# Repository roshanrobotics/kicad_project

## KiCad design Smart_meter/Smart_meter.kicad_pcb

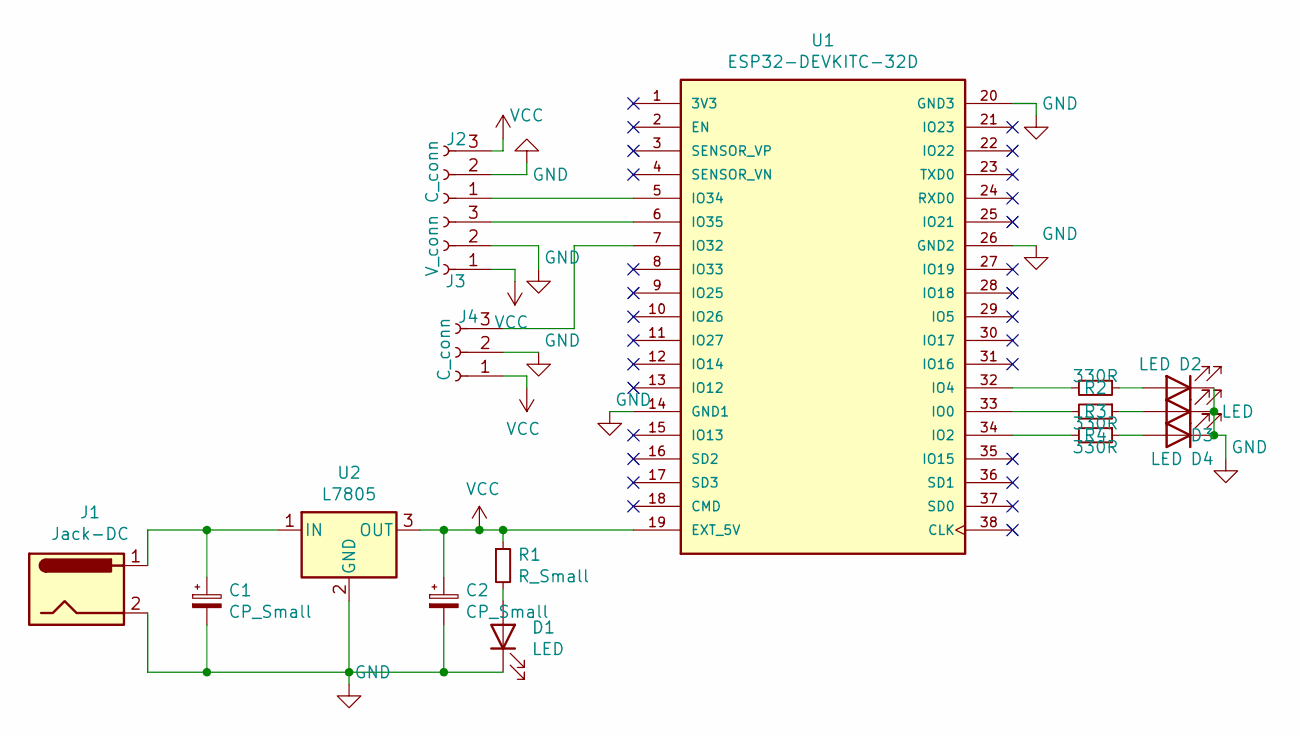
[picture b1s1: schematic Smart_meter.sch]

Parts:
C1, C2: CP_Small; CP_Radial_D5.0mm_P2.50mm
D1, D2, D3, D4: LED; LED_D5.0mm
J1: Jack-DC; BarrelJack_Horizontal
J2, J4: C_conn; PinHeader_1x03_P2.54mm_Vertical
J3: V_conn; PinHeader_1x03_P2.54mm_Vertical
R1: R_Small; R_Axial_DIN0207_L6.3mm_D2.5mm_P7.62mm_Horizontal
R2, R3, R4: 330R; R_Axial_DIN0207_L6.3mm_D2.5mm_P7.62mm_Horizontal
U1: ESP32-DEVKITC-32D; MODULE_ESP32-DEVKITC-32D; PARTREV 4
U2: L7805; TO-220-3_Vertical

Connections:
GND: C1.2, C2.2, D1.1 (K), D2.1 (K), D3.1 (K), D4.1 (K), J1.2, J2.2, J3.2, J4.2, U1.14 (GND1), U1.20 (GND3), U1.26 (GND2), U2.2 (GND)
unnamed: C1.1, J1.1, U2.1 (IN)
unnamed: D1.2 (A), R1.2
unnamed: D2.2 (A), R2.1
unnamed: D3.2 (A), R3.1
unnamed: D4.2 (A), R4.1
unnamed: J2.1, U1.5 (IO34)
unnamed: J3.3, U1.6 (IO35)
unnamed: J4.3, U1.7 (IO32)
unnamed: R2.2, U1.32 (IO4)
unnamed: R3.2, U1.33 (IO0)
unnamed: R4.2, U1.34 (IO2)
VCC: C2.1, J2.3, J3.1, J4.1, R1.1, U1.19 (EXT_5V), U2.3 (OUT)

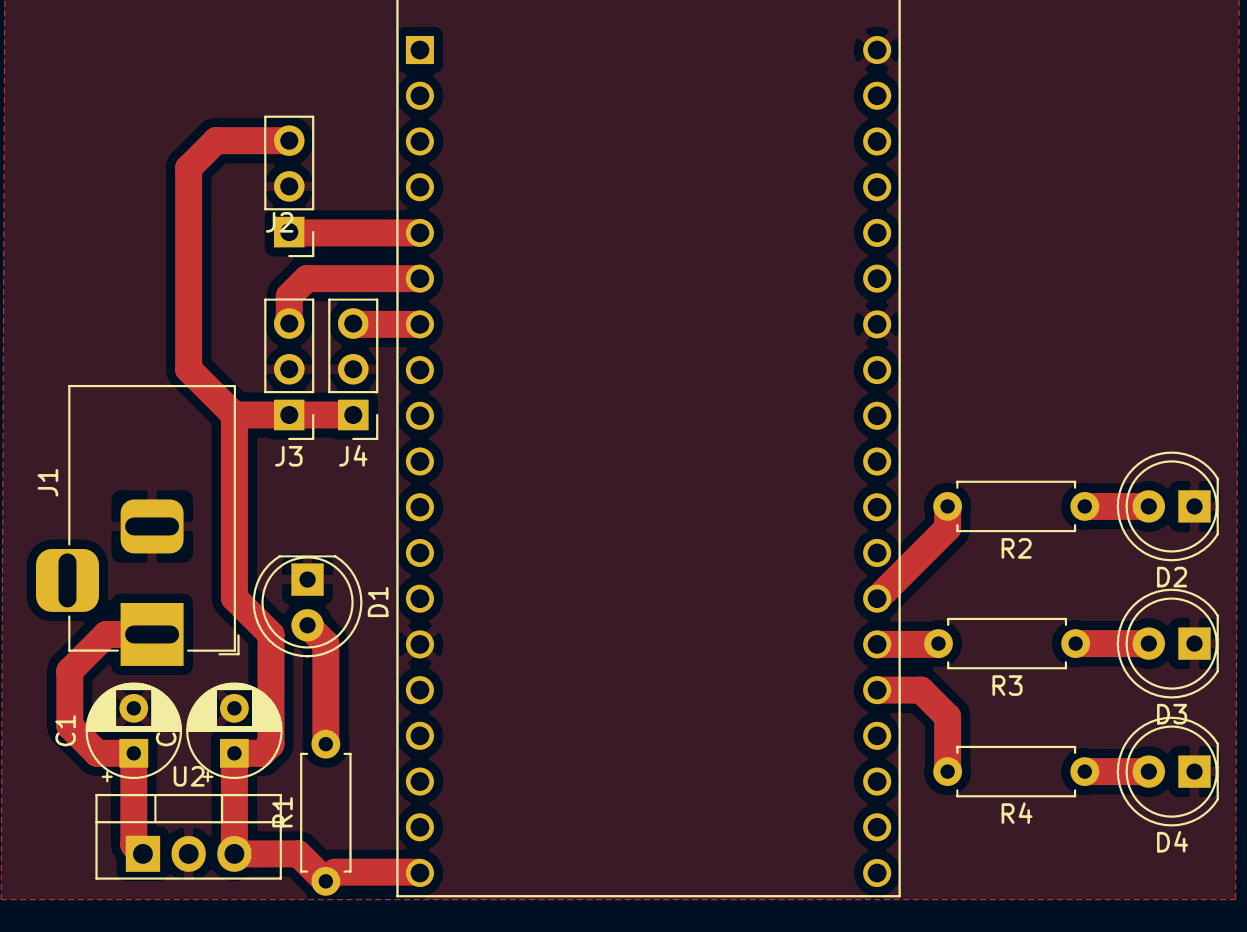
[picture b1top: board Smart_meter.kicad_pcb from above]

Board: 2 copper layers, 16 parts (0 on the bottom side), 13 nets.

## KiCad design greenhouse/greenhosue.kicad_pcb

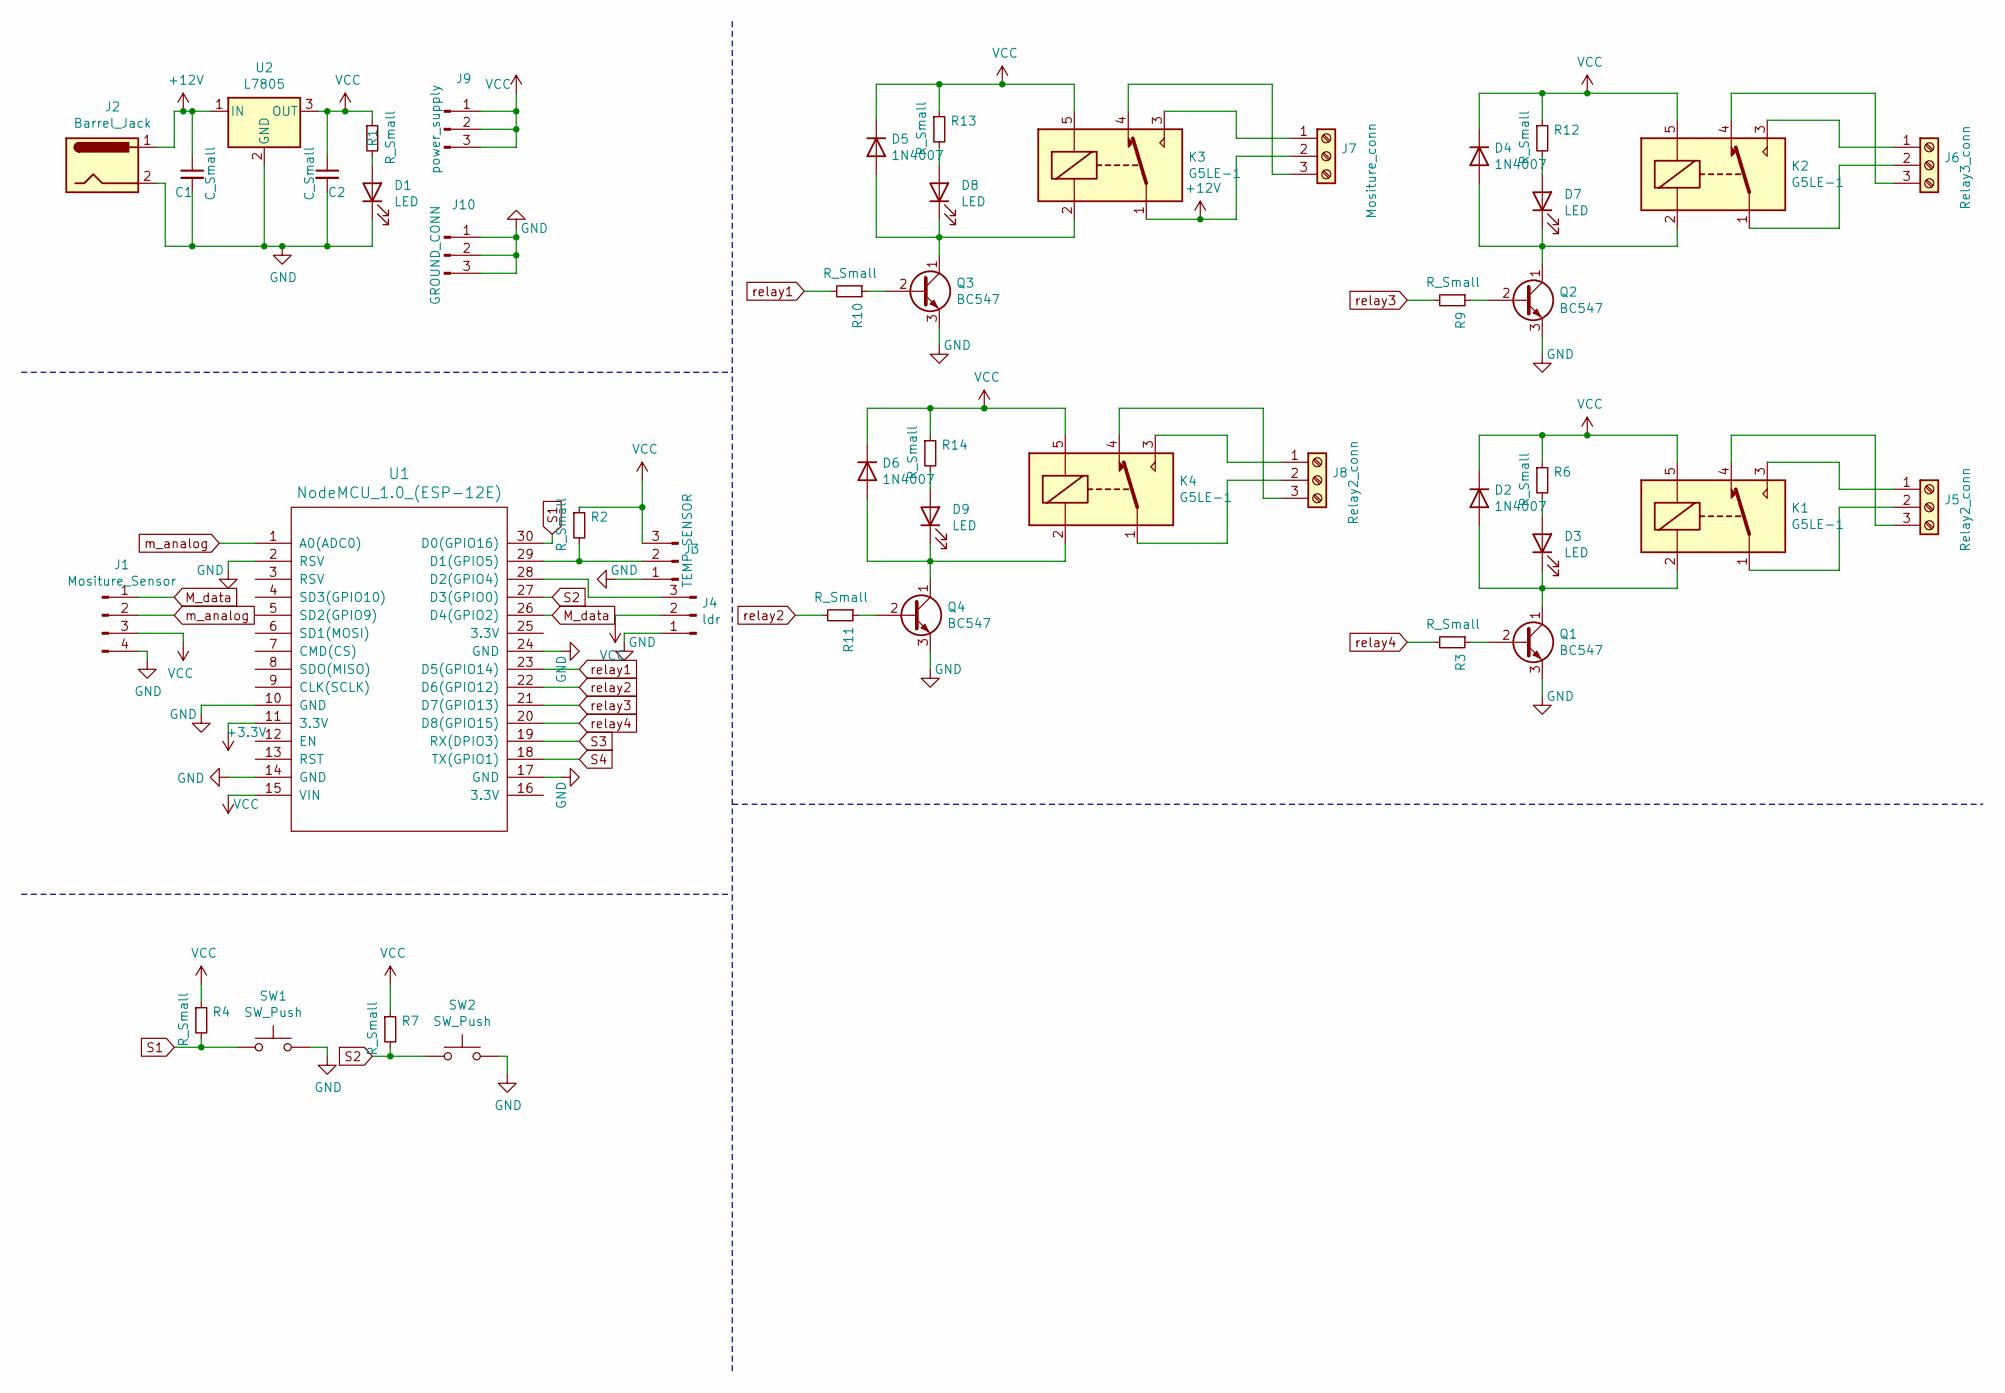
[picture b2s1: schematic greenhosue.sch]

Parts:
C1, C2: C_Small; CP_Radial_D6.3mm_P2.50mm
D1, D3, D7, D8, D9: LED; LED_D5.0mm
D2, D4, D5, D6: 1N4007; D_DO-41_SOD81_P10.16mm_Horizontal
J1: Mositure_Sensor; PinHeader_1x04_P2.54mm_Vertical
J2: Barrel_Jack; BarrelJack_Horizontal
J3: TEMP_SENSOR; PinHeader_1x03_P2.54mm_Vertical
J4: ldr; PinHeader_1x03_P2.54mm_Vertical
J5, J8: Relay2_conn; TerminalBlock_Phoenix_MKDS-1,5-3_1x03_P5.00mm_Horizontal
J6: Relay3_conn; TerminalBlock_Phoenix_MKDS-1,5-3_1x03_P5.00mm_Horizontal
J7: Mositure_conn; TerminalBlock_Phoenix_MKDS-1,5-3_1x03_P5.00mm_Horizontal
J9: power_supply; PinHeader_1x03_P2.54mm_Vertical
J10: GROUND_CONN; PinHeader_1x03_P2.54mm_Vertical
K1, K2, K3, K4: G5LE-1; Relay_SPDT_Omron-G5LE-1
Q1, Q2, Q3, Q4: BC547; TO-92_Inline_Wide
R1, R2, R3, R4, R6, R7, R9, R10, R11, R12, R13, R14: R_Small; R_Axial_DIN0207_L6.3mm_D2.5mm_P7.62mm_Horizontal
SW1, SW2: SW_Push; SW_PUSH_6mm
U1: NodeMCU_1.0_(ESP-12E); NodeMCU-LoLinV3
U2: L7805; TO-220-3_Vertical

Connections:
+3V3: U1.11 (3.3V)
+12V: C1.1, J2.1, J7.2, K3.1, U2.1 (IN)
GND: C1.2, C2.2, D1.1 (K), J1.4, J2.2, J3.1, J4.1, J10.1, J10.2, J10.3, Q1.3 (E), Q2.3 (E), Q3.3 (E), Q4.3 (E), SW1.2, SW2.2, U1.2 (RSV), U1.10 (GND), U1.14 (GND), U1.17 (GND), U1.24 (GND), U2.2 (GND)
M_data: J1.1, U1.26 (D4(GPIO2))
unnamed: D1.2 (A), R1.2
unnamed: D2.2 (A), D3.1 (K), K1.2, Q1.1 (C)
unnamed: D3.2 (A), R6.2
unnamed: D4.2 (A), D7.1 (K), K2.2, Q2.1 (C)
unnamed: D5.2 (A), D8.1 (K), K3.2, Q3.1 (C)
unnamed: D6.2 (A), D9.1 (K), K4.2, Q4.1 (C)
unnamed: D7.2 (A), R12.2
unnamed: D8.2 (A), R13.2
unnamed: D9.2 (A), R14.2
unnamed: J3.2, R2.2, U1.29 (D1(GPIO5))
unnamed: J4.3, U1.28 (D2(GPIO4))
unnamed: J5.1, K1.3
unnamed: J5.2, K1.1
unnamed: J5.3, K1.4
unnamed: J6.1, K2.3
unnamed: J6.2, K2.1
unnamed: J6.3, K2.4
unnamed: J7.1, K3.3
unnamed: J7.3, K3.4
unnamed: J8.1, K4.3
unnamed: J8.2, K4.1
unnamed: J8.3, K4.4
unnamed: Q1.2 (B), R3.1
unnamed: Q2.2 (B), R9.1
unnamed: Q3.2 (B), R10.1
unnamed: Q4.2 (B), R11.1
S1: R4.2, SW1.1, U1.30 (D0(GPIO16))
S2: R7.2, SW2.1, U1.27 (D3(GPIO0))
S3: U1.19 (RX(DPIO3))
S4: U1.18 (TX(GPIO1))
VCC: C2.1, D2.1 (K), D4.1 (K), D5.1 (K), D6.1 (K), J1.3, J3.3, J4.2, J9.1, J9.2, J9.3, K1.5, K2.5, K3.5, K4.5, R1.1, R2.1, R4.1, R6.1, R7.1, R12.1, R13.1, R14.1, U1.15 (VIN), U2.3 (OUT)
m_analog: J1.2, U1.1 (A0(ADC0))
relay1: R10.2, U1.23 (D5(GPIO14))
relay2: R11.2, U1.22 (D6(GPIO12))
relay3: R9.2, U1.21 (D7(GPIO13))
relay4: R3.2, U1.20 (D8(GPIO15))

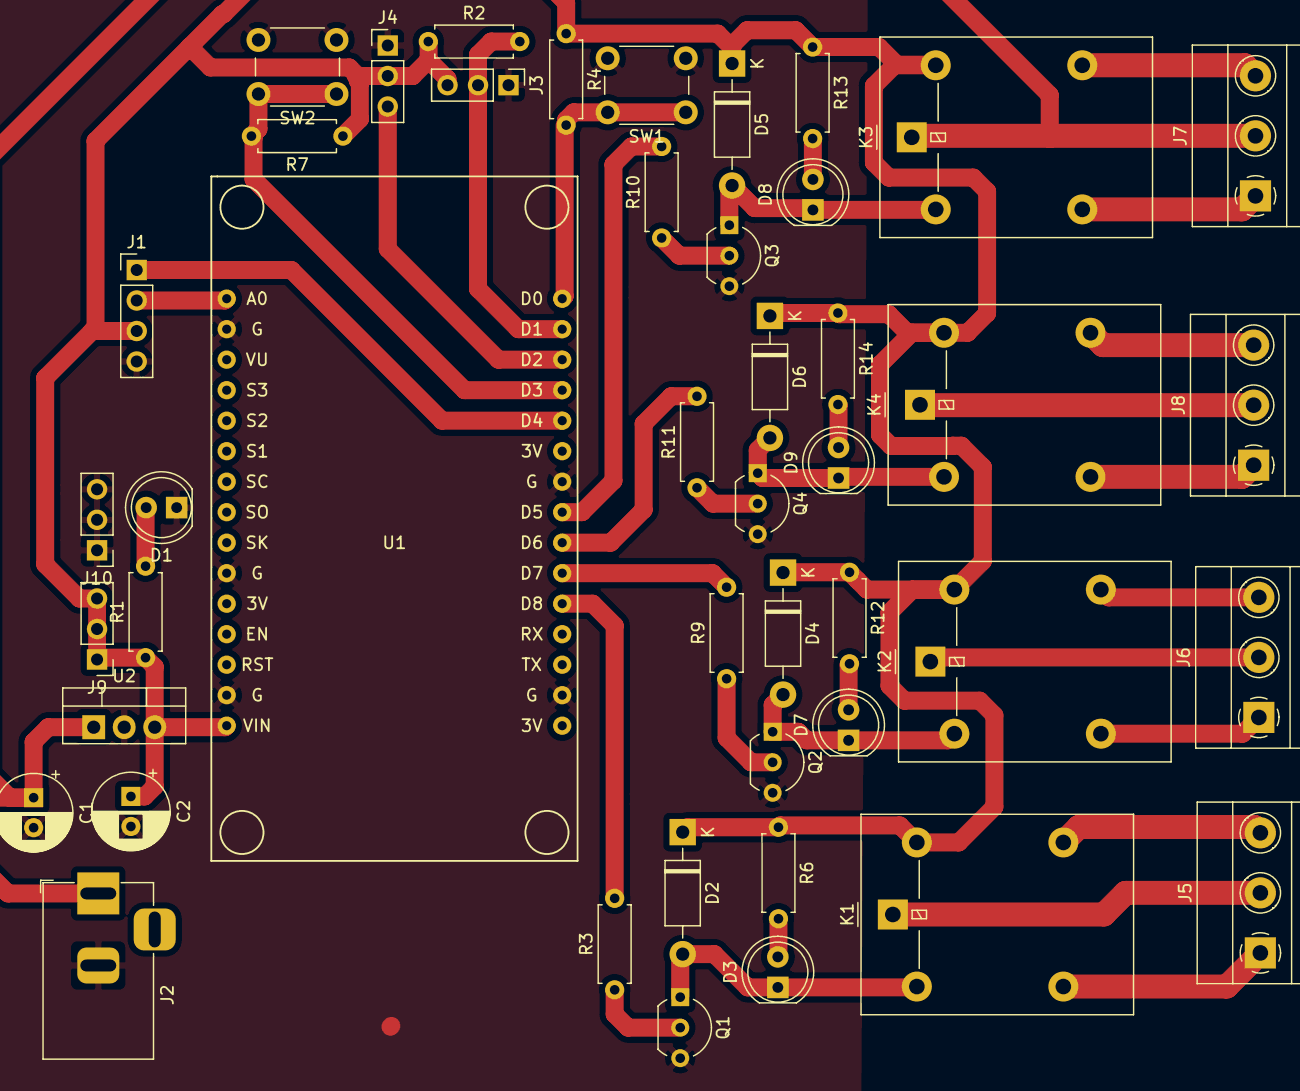
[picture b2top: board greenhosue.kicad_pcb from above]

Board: 2 copper layers, 45 parts (0 on the bottom side), 37 nets.

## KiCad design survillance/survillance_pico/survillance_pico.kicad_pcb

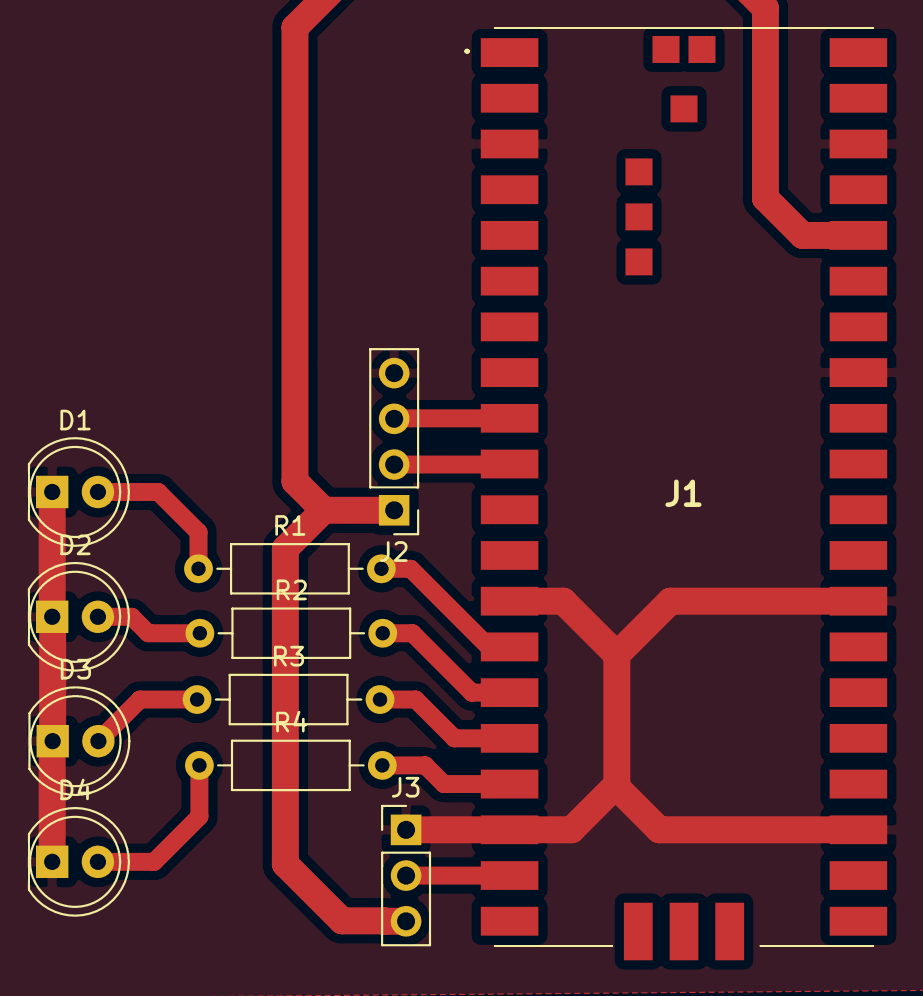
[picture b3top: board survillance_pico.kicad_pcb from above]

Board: 2 copper layers, 11 parts (0 on the bottom side), 13 nets.

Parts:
D1, D2, D3, D4: LED; LED_D5.0mm
J1: PICO
J2: Conn_01x04_Male; PinHeader_1x04_P2.54mm_Vertical
J3: Conn_01x03_Male; PinHeader_1x03_P2.54mm_Vertical
R1, R2, R3, R4: R_Small; R_Axial_DIN0207_L6.3mm_D2.5mm_P10.16mm_Horizontal

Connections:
+5V: J1.36, J2.1, J3.3
GND: D1.1, D2.1, D3.1, D4.1, J1.3, J1.13, J1.18, J1.23, J1.28, J1.33, J1.38, J2.4, J3.1
LED1: J1.17, R4.2
LED2: J1.16, R3.2
LED3: J1.15, R2.2
LED4: J1.14, R1.2
unnamed: D1.2, R1.1
unnamed: D2.2, R2.1
unnamed: D3.2, R3.1
unnamed: D4.2, R4.1
PICO_SCL: J1.10, J2.2
PICO_SDA: J1.9, J2.3
PIR: J1.19, J3.2

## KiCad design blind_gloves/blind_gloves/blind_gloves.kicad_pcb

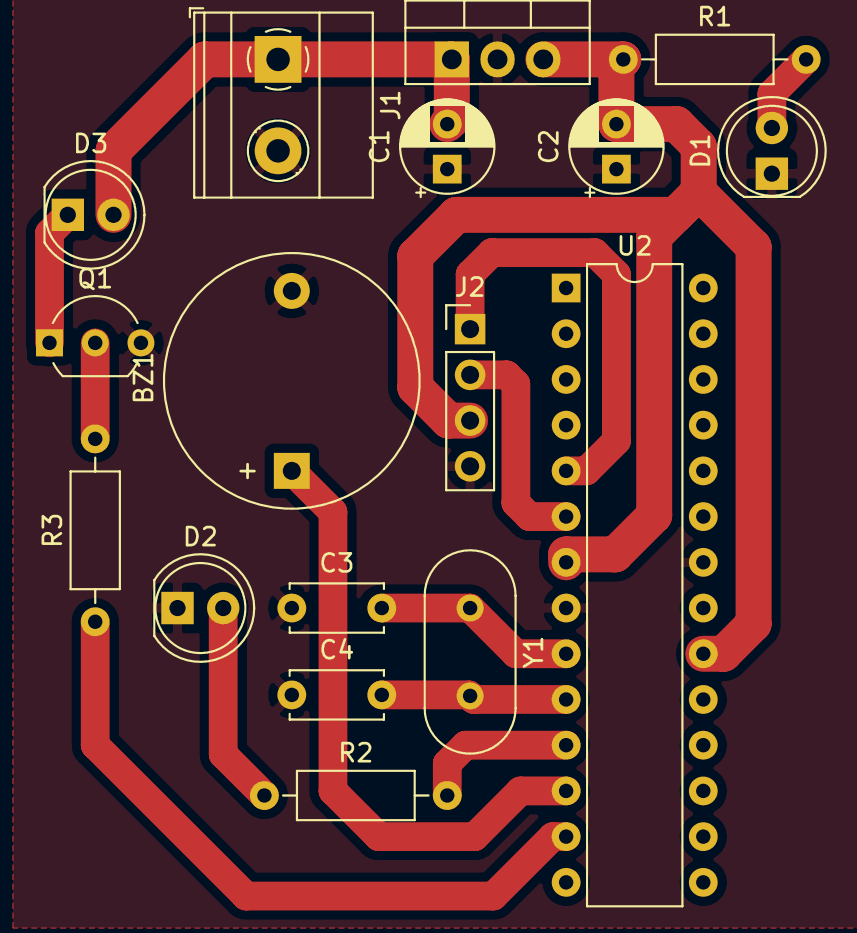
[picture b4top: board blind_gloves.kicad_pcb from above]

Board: 2 copper layers, 17 parts (0 on the bottom side), 14 nets.

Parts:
BZ1: Buzzer; Buzzer_D14mm_H7mm_P10mm
C1: 10uf; CP_Radial_D5.0mm_P2.50mm
C2: 100uf; CP_Radial_D5.0mm_P2.50mm
C3, C4: 22pf; C_Disc_D5.0mm_W2.5mm_P5.00mm
D1, D2, D3: LED; LED_D5.0mm
J1: Battery Connector; TerminalBlock_Phoenix_MKDS-1,5-2-5.08_1x02_P5.08mm_Horizont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
J2: Ultrasonic connector; PinHeader_1x04_P2.54mm_Vertical
Q1: BC547; TO-92_Inline_Wide
R1: 330ohm; R_Axial_DIN0207_L6.3mm_D2.5mm_P10.16mm_Horizontal
R2: 330R; R_Axial_DIN0207_L6.3mm_D2.5mm_P10.16mm_Horizontal
R3: 1k; R_Axial_DIN0207_L6.3mm_D2.5mm_P10.16mm_Horizontal
U1: L7805; TO-220-3_Vertical
U2: ATmega328P-PU; DIP-28_W7.62mm
Y1: 16mhz; Crystal_HC49-U_Vertical

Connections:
+5V: C2.2, J2.3, R1.1, U1.3, U2.7, U2.20
+9V: C1.2, D3.2, J1.1, U1.1
GND: BZ1.2, C1.1, C2.1, C3.1, C4.1, D1.1, D2.1, J1.2, J2.4, Q1.3, U1.2, U2.8, U2.22
unnamed: BZ1.1, U2.12
unnamed: C3.2, U2.9, Y1.1
unnamed: C4.2, U2.10, Y1.2
unnamed: D1.2, R1.2
unnamed: D2.2, R2.1
unnamed: D3.1, Q1.1
unnamed: J2.1, U2.5
unnamed: J2.2, U2.6
unnamed: Q1.2, R3.2
unnamed: R2.2, U2.11
unnamed: R3.1, U2.13

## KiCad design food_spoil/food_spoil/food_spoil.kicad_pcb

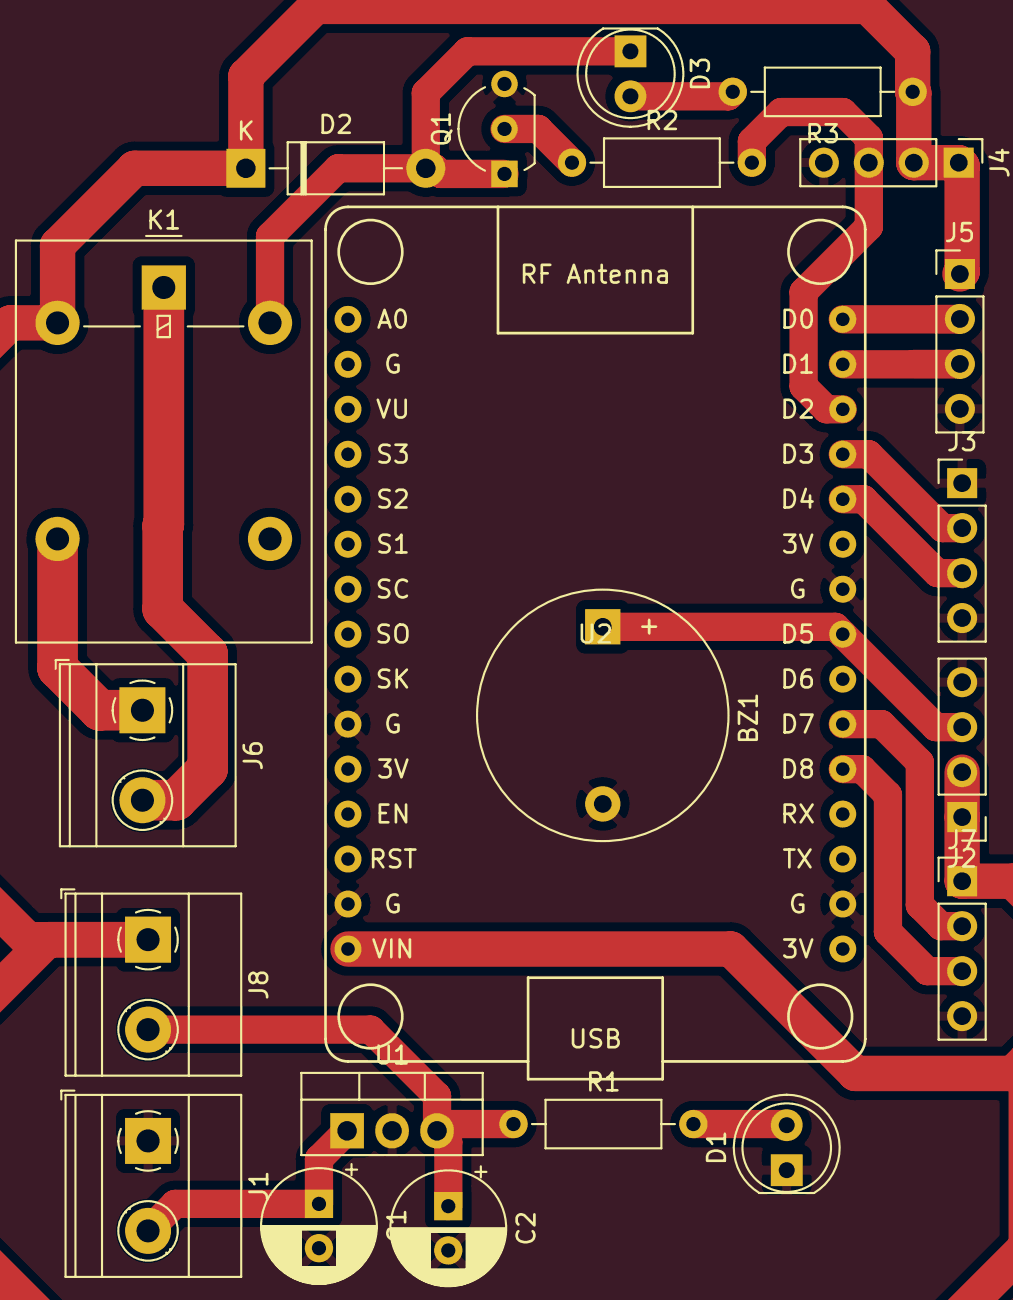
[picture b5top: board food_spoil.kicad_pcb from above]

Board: 2 copper layers, 21 parts (0 on the bottom side), 18 nets.

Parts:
BZ1: Buzzer; Buzzer_D14mm_H7mm_P10mm
C1, C2: C_Small; CP_Radial_D6.3mm_P2.50mm
D1, D3: LED; LED_D5.0mm
D2: 1N4007; D_DO-41_SOD81_P10.16mm_Horizontal
J1, J8: Screw_Terminal_01x02; TerminalBlock_Phoenix_MKDS-1,5-2-5.08_1x02_P5.08mm_Horizont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
J2: BUZZER_CONN; PinHeader_1x04_P2.54mm_Vertical
J3: indicator; PinHeader_1x04_P2.54mm_Vertical
J4: control_CONNECTOR; PinHeader_1x04_P2.54mm_Vertical
J5: GSm_connector; PinHeader_1x04_P2.54mm_Vertical
J6: AC_SUPPLY; TerminalBlock_Phoenix_MKDS-1,5-2-5.08_1x02_P5.08mm_Horizont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
J7: LCD_con; PinHeader_1x04_P2.54mm_Vertical
K1: G5LE-1; Relay_SPDT_Omron-G5LE-1
Q1: BC547; TO-92L_Inline_Wide
R1, R2, R3: R_Small; R_Axial_DIN0207_L6.3mm_D2.5mm_P10.16mm_Horizontal
U1: L7805; TO-220-3_Vertical
U2: NodeMCU_1.0_(ESP-12E); NodeMCU1.0(12-E)

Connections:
+5V: D2.1, J2.1, J2.2, J4.1, J4.2, J5.1, J7.1, J8.1, K1.2, R3.1, U2.15
A0_sensor: J5.2, U2.30
D0_Sensor: J5.3, U2.29
Engine: J4.3, R2.2, U2.28
GND: BZ1.2, C1.2, C2.2, D1.1, J1.1, J2.4, J3.1, J3.4, J4.4, J5.4, J7.4, Q1.3, U1.2, U2.10, U2.14, U2.17, U2.24
unnamed: C1.1, J1.2, U1.1
unnamed: C2.1, J8.2, R1.1, U1.3
unnamed: D1.2, R1.2
unnamed: D2.2, D3.1, K1.5, Q1.1
unnamed: D3.2, R3.2
unnamed: J6.1, K1.3
unnamed: J6.2, K1.1
unnamed: Q1.2, R2.1
SCL: J7.3, U2.20
SDA: J7.2, U2.21
buzz: BZ1.1, J2.3, U2.23
green_led: J3.3, U2.26
red_led: J3.2, U2.27

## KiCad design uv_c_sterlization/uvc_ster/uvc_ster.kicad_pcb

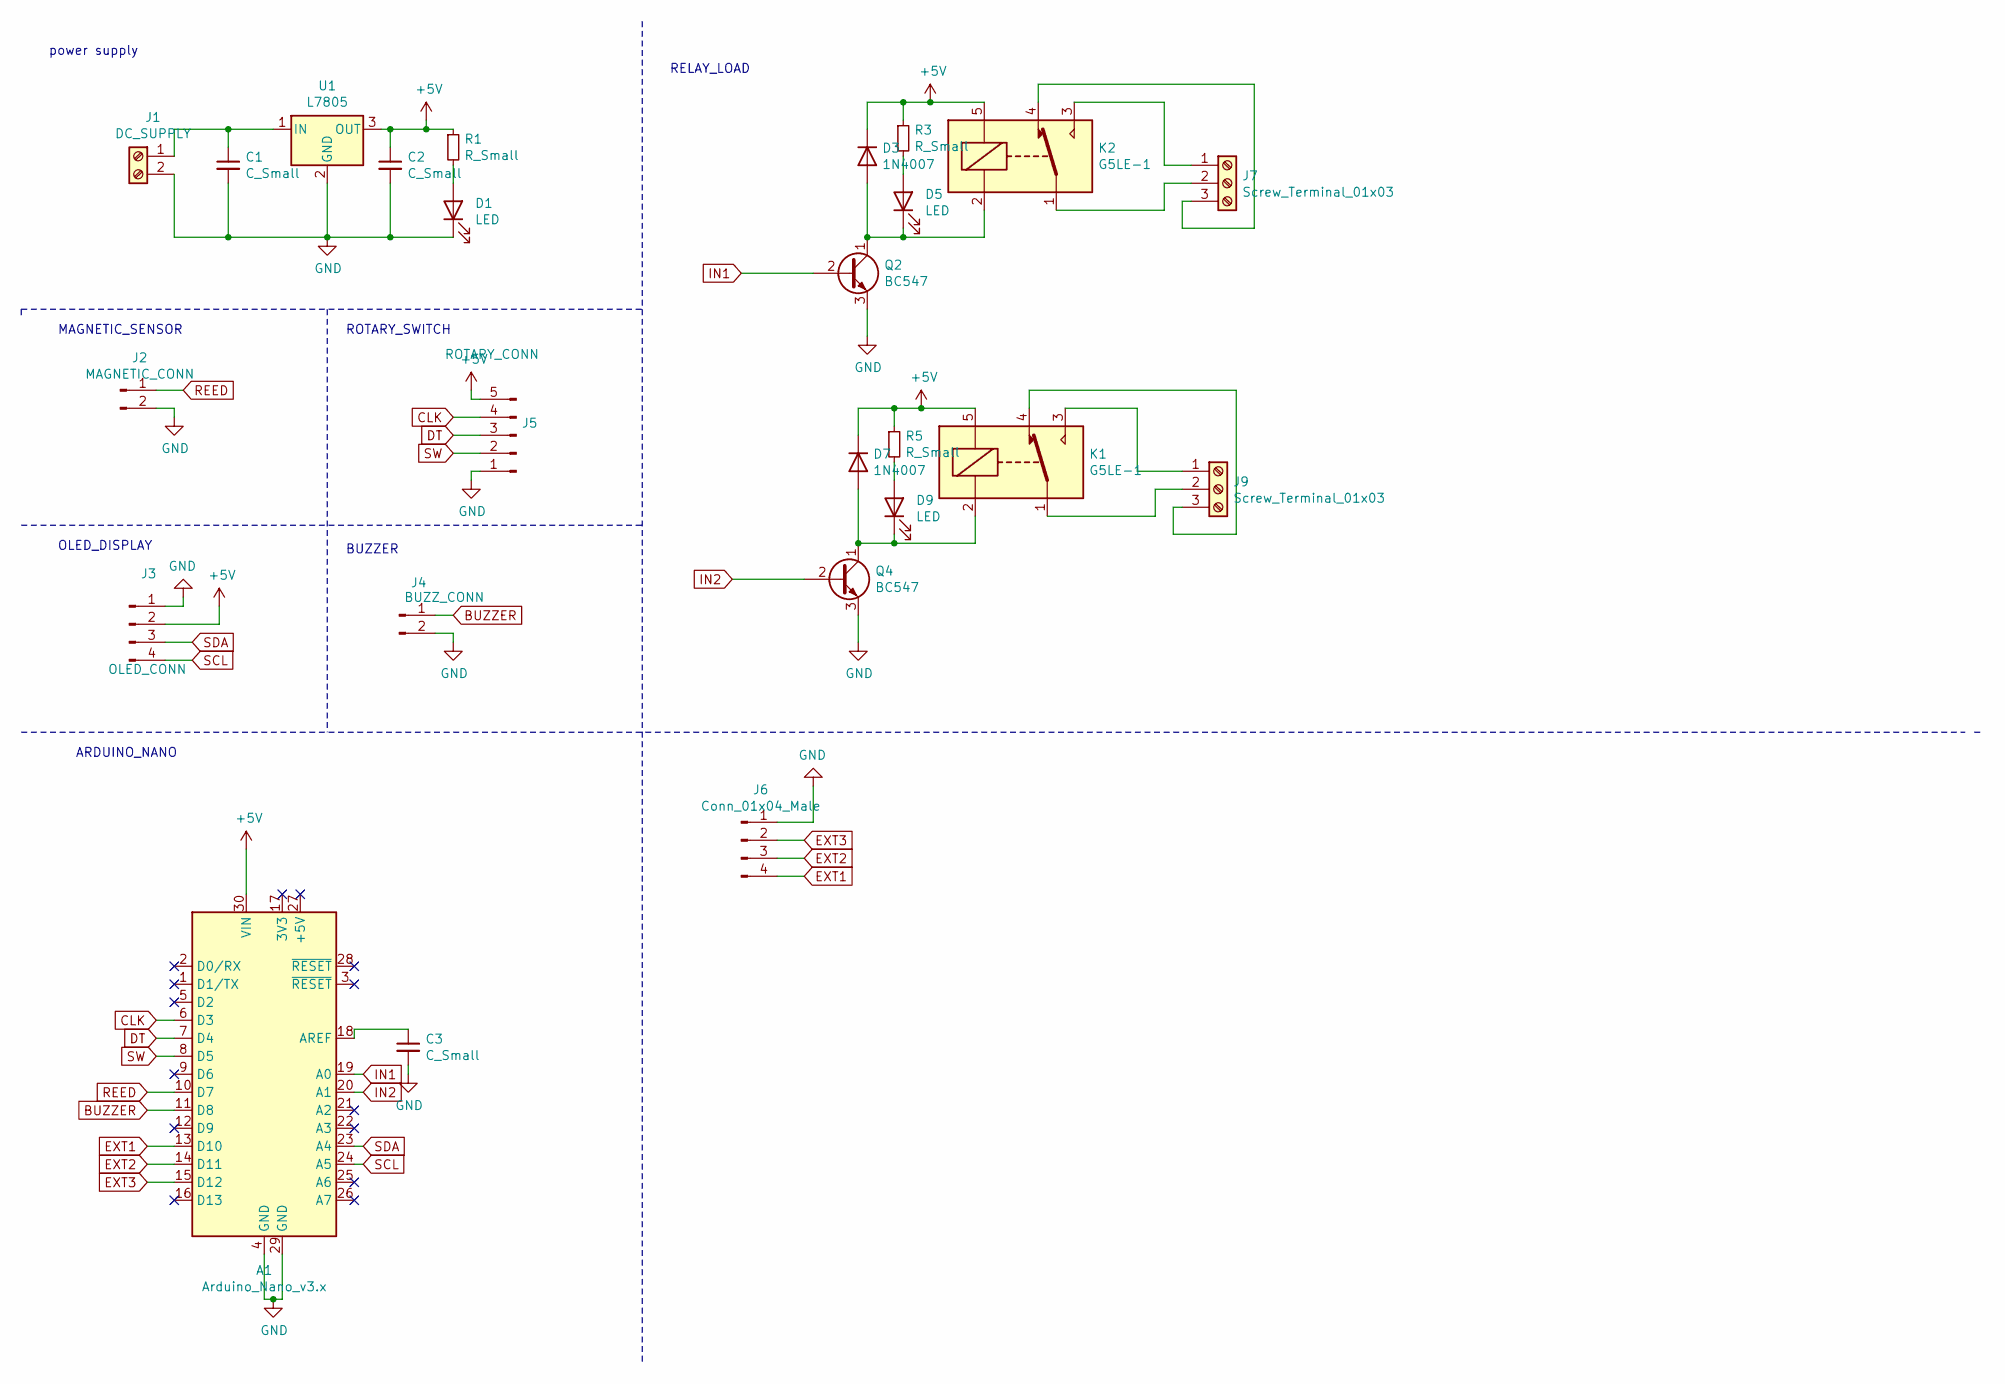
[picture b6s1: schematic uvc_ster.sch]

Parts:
A1: Arduino_Nano_v3.x; Arduino_Nano
C1, C2: C_Small; CP_Radial_D5.0mm_P2.50mm
C3: C_Small; C_Disc_D5.0mm_W2.5mm_P2.50mm
D1, D5, D9: LED; LED_D5.0mm
D3, D7: 1N4007; D_DO-41_SOD81_P10.16mm_Horizontal
J1: DC_SUPPLY; TerminalBlock_Phoenix_MKDS-1,5-2_1x02_P5.00mm_Horizontal
J2: MAGNETIC_CONN; TerminalBlock_Phoenix_MKDS-1,5-2_1x02_P5.00mm_Horizontal
J3: OLED_CONN; TerminalBlock_Phoenix_MKDS-1,5-4_1x04_P5.00mm_Horizontal
J4: BUZZ_CONN; TerminalBlock_Phoenix_MKDS-1,5-2_1x02_P5.00mm_Horizontal
J5: ROTARY_CONN; TerminalBlock_Phoenix_MKDS-1,5-5_1x05_P5.00mm_Horizontal
J6: Conn_01x04_Male; PinHeader_1x04_P2.54mm_Vertical
J7, J9: Screw_Terminal_01x03; TerminalBlock_Phoenix_MKDS-1,5-3_1x03_P5.00mm_Horizontal
K1, K2: G5LE-1; Relay_SPDT_Omron-G5LE-1
Q2, Q4: BC547; TO-92L_Wide
R1, R3, R5: R_Small; R_Axial_DIN0207_L6.3mm_D2.5mm_P7.62mm_Horizontal
U1: L7805; TO-220-3_Vertical

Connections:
+5V: A1.30 (VIN), C2.1, D3.1 (K), D7.1 (K), J3.2, J5.5, K1.5, K2.5, R1.1, R3.1, R5.1, U1.3 (OUT)
BUZZER: A1.11 (D8), J4.1
CLK: A1.6 (D3), J5.4
DT: A1.7 (D4), J5.3
EXT1: A1.13 (D10), J6.4
EXT2: A1.14 (D11), J6.3
EXT3: A1.15 (D12), J6.2
GND: A1.4 (GND), A1.29 (GND), C1.2, C2.2, C3.2, D1.1 (K), J1.2, J2.2, J3.1, J4.2, J5.1, J6.1, Q2.3 (E), Q4.3 (E), U1.2 (GND)
IN1: A1.19 (A0), Q2.2 (B)
IN2: A1.20 (A1), Q4.2 (B)
unnamed: A1.18 (AREF), C3.1
unnamed: C1.1, J1.1, U1.1 (IN)
unnamed: D1.2 (A), R1.2
unnamed: D3.2 (A), D5.1 (K), K2.2, Q2.1 (C)
unnamed: D5.2 (A), R3.2
unnamed: D7.2 (A), D9.1 (K), K1.2, Q4.1 (C)
unnamed: D9.2 (A), R5.2
unnamed: J7.1, K2.3
unnamed: J7.2, K2.1
unnamed: J7.3, K2.4
unnamed: J9.1, K1.3
unnamed: J9.2, K1.1
unnamed: J9.3, K1.4
REED: A1.10 (D7), J2.1
SCL: A1.24 (A5), J3.4
SDA: A1.23 (A4), J3.3
SW: A1.8 (D5), J5.2

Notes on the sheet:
power supply
MAGNETIC_SENSOR
ROTARY_SWITCH
BUZZER
OLED_DISPLAY
ARDUINO_NANO
RELAY_LOAD

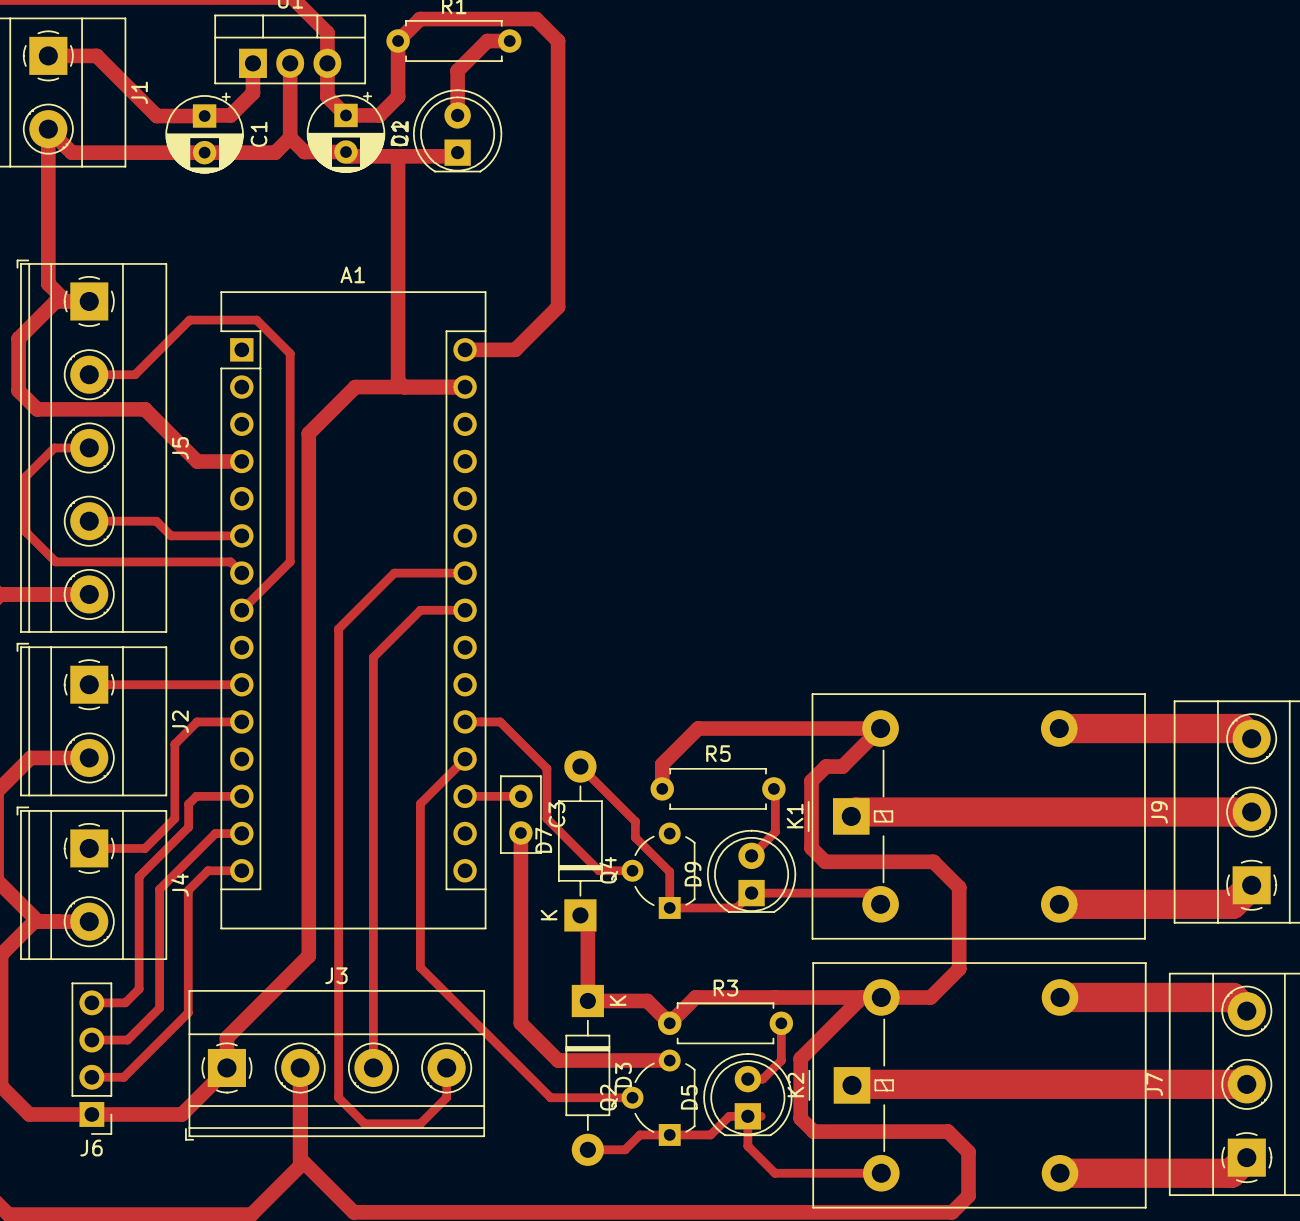
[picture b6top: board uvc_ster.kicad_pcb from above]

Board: 2 copper layers, 25 parts (0 on the bottom side), 27 nets.

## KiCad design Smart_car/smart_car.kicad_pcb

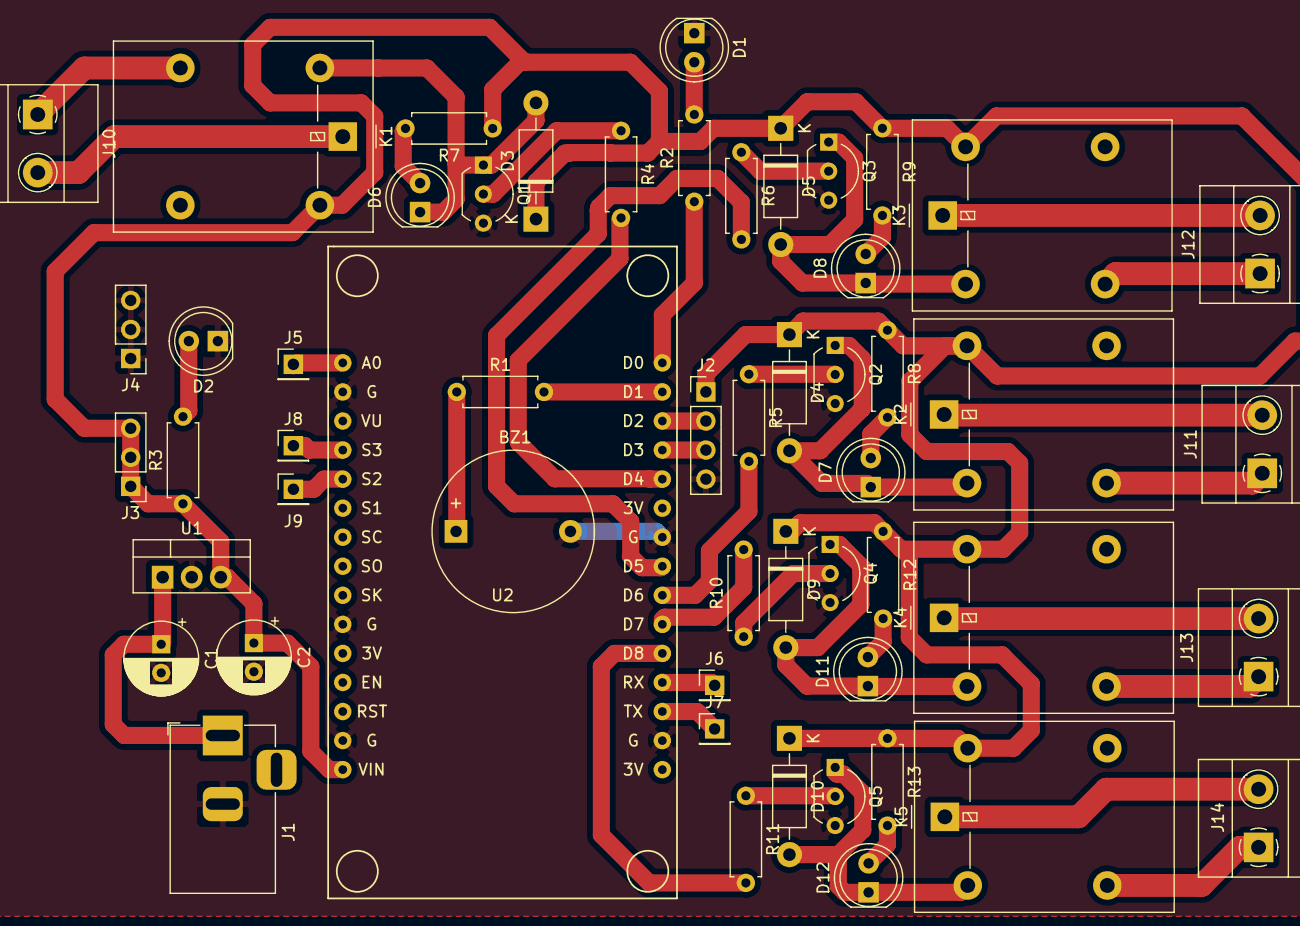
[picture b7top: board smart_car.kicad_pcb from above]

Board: 2 copper layers, 54 parts (0 on the bottom side), 45 nets.

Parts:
BZ1: Buzzer; Buzzer_D14mm_H7mm_P10mm
C1, C2: C_Small; CP_Radial_D6.3mm_P2.50mm
D1, D2, D6, D7, D8, D11, D12: LED; LED_D5.0mm
D3, D4, D5, D9, D10: 1N4007; D_DO-41_SOD81_P10.16mm_Horizontal
J1: Barrel_Jack; BarrelJack_Horizontal
J2: ultrasonic; PinHeader_1x04_P2.54mm_Vertical
J3: power_supply; PinHeader_1x03_P2.54mm_Vertical
J4: GROUND_CONN; PinHeader_1x03_P2.54mm_Vertical
J5: expin; PinHeader_1x01_P2.54mm_Vertical
J6: expin1; PinHeader_1x01_P2.54mm_Vertical
J7: expin2; PinHeader_1x01_P2.54mm_Vertical
J8: expin3; PinHeader_1x01_P2.54mm_Vertical
J9: expin4; PinHeader_1x01_P2.54mm_Vertical
J10: r5_conn; TerminalBlock_Phoenix_MKDS-1,5-2-5.08_1x02_P5.08mm_Horizont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
J11: r2_conn; TerminalBlock_Phoenix_MKDS-1,5-2-5.08_1x02_P5.08mm_Horizont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
J12: r1_conn; TerminalBlock_Phoenix_MKDS-1,5-2-5.08_1x02_P5.08mm_Horizont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
J13: r3_conn; TerminalBlock_Phoenix_MKDS-1,5-2-5.08_1x02_P5.08mm_Horizont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
J14: r4_conn; TerminalBlock_Phoenix_MKDS-1,5-2-5.08_1x02_P5.08mm_Horizont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
K1, K2, K3, K4, K5: G5LE-1; Relay_SPDT_Omron-G5LE-1
Q1, Q2, Q3, Q4, Q5: BC547; TO-92_Inline_Wide
R1, R2, R3, R4, R5, R6, R7, R8, R9, R10, R11, R12, R13: R_Small; R_Axial_DIN0207_L6.3mm_D2.5mm_P7.62mm_Horizontal
U1: L7805; TO-220-3_Vertical
U2: NodeMCU_1.0_(ESP-12E); NodeMCU-LoLinV3

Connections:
GND: BZ1.2, C1.2, C2.2, D1.1, D2.1, J1.2, J2.4, J4.1, J4.2, J4.3, Q1.3, Q2.3, Q3.3, Q4.3, Q5.3, U1.2, U2.2, U2.10, U2.14, U2.17, U2.24
unnamed: BZ1.1, R1.1
unnamed: C1.1, J1.1, U1.1
unnamed: D1.2, R2.2
unnamed: D2.2, R3.2
unnamed: D3.2, D6.1, K1.2, Q1.1
unnamed: D4.2, D7.1, K2.2, Q2.1
unnamed: D5.2, D8.1, K3.2, Q3.1
unnamed: D6.2, R7.2
unnamed: D7.2, R8.2
unnamed: D8.2, R9.2
unnamed: D10.2, D12.1, K5.2, Q5.1
unnamed: D9.2, D11.1, K4.2, Q4.1
unnamed: D11.2, R12.2
unnamed: D12.2, R13.2
unnamed: J10.1, K1.3
unnamed: J10.2, K1.1
unnamed: J11.1, K2.3
unnamed: J11.2, K2.1
unnamed: J12.1, K3.3
unnamed: J12.2, K3.1
unnamed: J13.1, K4.3
unnamed: J13.2, K4.1
unnamed: J14.1, K5.3
unnamed: J14.2, K5.1
unnamed: Q1.2, R4.1
unnamed: Q2.2, R5.1
unnamed: Q3.2, R6.1
unnamed: Q4.2, R10.1
unnamed: Q5.2, R11.1
VCC: C2.1, D3.1, D4.1, D5.1, D9.1, D10.1, J2.1, J3.1, J3.2, J3.3, K1.5, K2.5, K3.5, K4.5, K5.5, R3.1, R7.1, R8.1, R9.1, R12.1, R13.1, U1.3, U2.15
buzz: R1.2, U2.29
echo: J2.2, U2.28
espin1: J6.1, U2.19
espin2: J7.1, U2.18
expin: J5.1, U2.1
expin3: J8.1, U2.4
expin4: J9.1, U2.5
headlamp: R2.1, U2.30
relay1: R6.2, U2.23
relay2: R5.2, U2.22
relay3: R10.2, U2.21
relay4: R11.2, U2.20
relay5: R4.2, U2.26
trigger: J2.3, U2.27

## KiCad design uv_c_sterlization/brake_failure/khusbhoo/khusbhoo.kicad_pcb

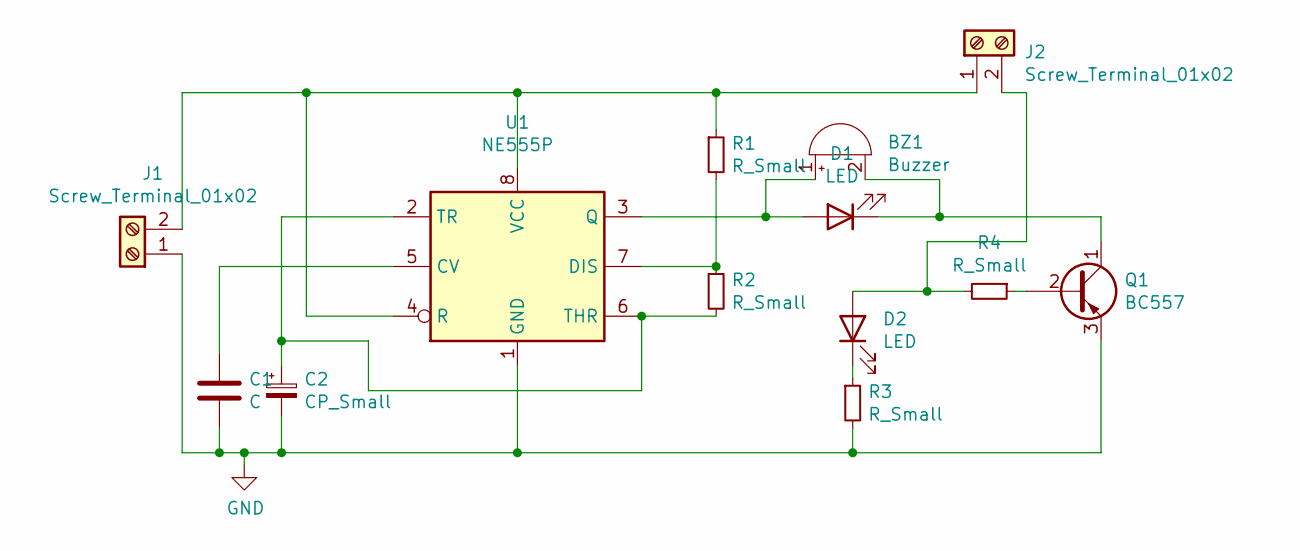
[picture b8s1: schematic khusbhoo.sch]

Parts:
BZ1: Buzzer; Buzzer_D14mm_H7mm_P10mm
C1: C; C_Disc_D5.0mm_W2.5mm_P5.00mm
C2: CP_Small; C_Radial_D5.0mm_H7.0mm_P2.00mm
D1, D2: LED; LED_D5.0mm
J1, J2: Screw_Terminal_01x02; TerminalBlock_Phoenix_MKDS-1,5-2_1x02_P5.00mm_Horizontal
Q1: BC557; TO-92_Wide
R1, R2, R3, R4: R_Small; R_Axial_DIN0411_L9.9mm_D3.6mm_P12.70mm_Horizontal
U1: NE555P; DIP-8_W7.62mm

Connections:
GND: C1.2, C2.2, J1.1, Q1.3 (E), R3.2, U1.1 (GND)
unnamed: BZ1.1 (-), D1.2 (A), U1.3 (Q)
unnamed: BZ1.2 (+), D1.1 (K), Q1.1 (C)
unnamed: C1.1, U1.5 (CV)
unnamed: C2.1, R2.2, U1.2 (TR), U1.6 (THR)
unnamed: D2.1 (K), R3.1
unnamed: D2.2 (A), J2.2, R4.2
unnamed: J1.2, J2.1, R1.1, U1.4 (R), U1.8 (VCC)
unnamed: Q1.2 (B), R4.1
unnamed: R1.2, R2.1, U1.7 (DIS)
